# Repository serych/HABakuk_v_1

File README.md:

# HABakuk Pico Balloon Tracker Board

## Introduction:

Design of this board is based on excelent Alain's (K1FM) [K1FM-Pico-Balloon version 1.3](https://github.com/adecarolis).  Why I didn't use Alain's board directly and made my own PCB forked from his design? I was thinking about WSPR balloon tracker design for a long time (approximately 2-3 years) and I wanted simple board with ATmega328, Si5351 and Ublox GPS with possibility to switch peripheries off. From the board designs I found on the Internet, K1FM board met my original ideas the most but:  
- I wanted to power the board by solar panels via MPPT regulator (theorethicaly only two 50 x 25 mm panels would be enought to supply the board)
- I wanted the HF filter, but bypassable to test if the signal penetration is better with or without the filter 
- I'm designing my boards in KiCAD now, so I wanted to redraw the design completely (it is better than trying to import Eagle files) 

## Board construction:
The board includes MPPT power converter based on the SPV1040 chip and the values of the discrete components around it are calculated using [STMicroelectronics eDesignSuite](https://eds.st.com/photovoltaic/) using input parameters Voc = 1200 mV, Imp = 500 mA (measured on two solar panels in series) and Vmp = 930 mV, Imp = 450 mA (my estimation). There is connector for THT electrolytic capacitor serving as the energy store on the board. 

HF filter can be bypassed using **JP1** by scratching off solder jumper contact 1 (which is bridged on PCB by default) and soldering contact 3. 

I'm not sure if the measurement of solar panel voltage by the ATmega will not interfere with the SPV1040 power converter function, so I placed **JP2** on the board (bridged by default) which can be easily scratched off to break the (solar panel -> AD converter input) connection in the case of any problems.
                                                                                                          
The board is designed as 4 layers (only 3 layers used) thin PCB (it has thicknes of 0.8 mm only to reduce the weight of the PCB). Also there is filled zone (GND) only on one side of the board to reduce the weight. All the components except the Ublox GPS module are placed on the top side of the board to make the reflow soldering possible in the amateur conditions.  GPS module on the back side of the board should be soldered as the last component by the soldering iron.      

## Software: 
The recommended softwares are [OrionWSPR](https://github.com/ve3wmb/OrionWspr) or [GeminiWSPR](https://github.com/adecarolis/GeminiWspr)

## Production and real tests
The board will be ordered in [LJCPCB](https://jlcpcb.com/) and I will add here the link to reorder it.

**The board was not yet produced nor tested!** 

Jakub Šerých, serych@panska.cz, [https://jakub.serych.cz](https://jakub.serych.cz) (web only in Czech language)

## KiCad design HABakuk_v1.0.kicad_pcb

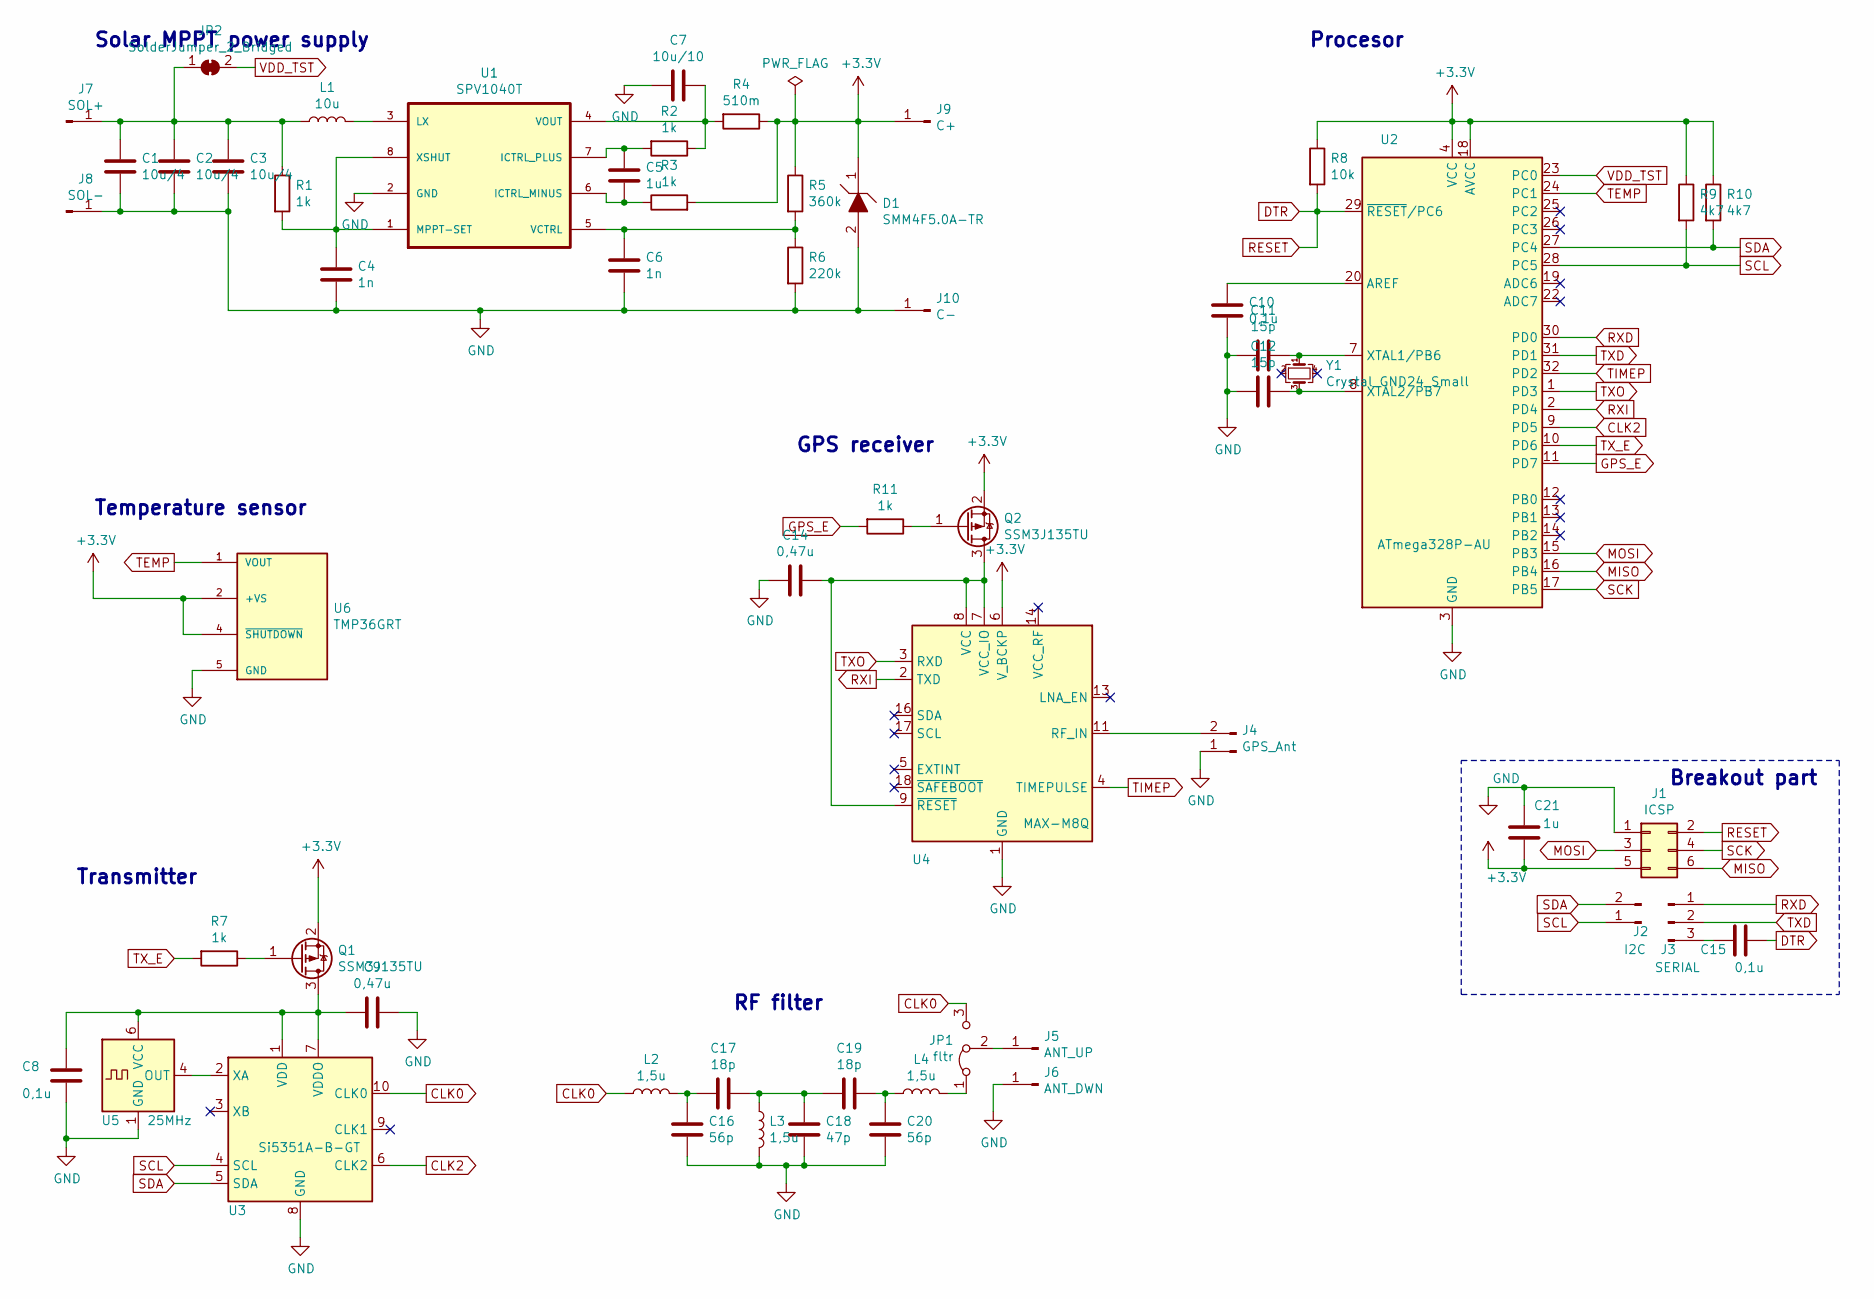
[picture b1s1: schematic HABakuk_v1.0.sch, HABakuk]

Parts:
C1, C2, C3: 10u/4; C_0603_1608Metric
C4, C6: 1n; C_0603_1608Metric
C5, C21: 1u; C_0603_1608Metric
C7: 10u/10; C_0805_2012Metric
C8, C10, C15: 0,1u; C_0603_1608Metric
C9, C14: 0,47u; C_0603_1608Metric
C11, C12: 15p; C_0603_1608Metric
C16, C20: 56p; C_0603_1608Metric
C17, C19: 18p; C_0603_1608Metric
C18: 47p; C_0603_1608Metric
D1: SMM4F5.0A-TR; STMITE; Mouser Part Number 511-SMM4F5.0A-TR
J1: ICSP; PinHeader_2x03_P2.54mm_Vertical
J2: I2C; PinHeader_1x02_P2.54mm_Vertical
J3: SERIAL; PinHeader_1x03_P2.54mm_Vertical
J4: GPS_Ant; PinHeader_1x02_P2.54mm_Vertical
J5: ANT_UP; PinHeader_1x01_P2.54mm_Vertical
J6: ANT_DWN; PinHeader_1x01_P2.54mm_Vertical
J7: SOL+; PinHeader_1x01_P2.54mm_Vertical
J8: SOL-; PinHeader_1x01_P2.54mm_Vertical
J9: C+; PinHeader_1x01_P2.54mm_Vertical
J10: C-; PinHeader_1x01_P2.54mm_Vertical
JP1: fltr; SolderJumper-3_P1.3mm_Bridged12_Pad1.0x1.5mm_NumberLabels
JP2: SolderJumper_2_Bridged; SolderJumper-2_P1.3mm_Bridged_Pad1.0x1.5mm
L1: 10u; L_Taiyo-Yuden_MD-3030
L2, L3, L4: 1,5u; L_0603_1608Metric
Q1, Q2: SSM3J135TU; SOT-23
R1, R2, R3, R7, R11: 1k; R_0603_1608Metric
R4: 510m; R_0603_1608Metric
R5: 360k; R_0603_1608Metric
R6: 220k; R_0603_1608Metric
R8: 10k; R_0603_1608Metric
R9, R10: 4k7; R_0603_1608Metric
U1: SPV1040T; TSSOP-8_4.4x3mm_P0.65mm
U2: ATmega328P-AU; TQFP-32_7x7mm_P0.8mm
U3: Si5351A-B-GT; MSOP-10_3x3mm_P0.5mm
U4: MAX-M8Q; ublox_MAX
U5: 25MHz; Oscillator_SMD_Kyocera_2520-6Pin_2.5x2.0mm
U6: TMP36GRT; SOT-23-5; PARTREV H
Y1: Crystal_GND24_Small; Crystal_SMD_5032-4Pin_5.0x3.2mm

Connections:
+3V3: C21.2, D1.1, J1.5, J9.1, Q1.2 (S), Q2.2 (S), R3.2, R4.1, R5.1, R8.1, R9.1, R10.1, U2.4 (VCC), U2.6 (VCC), U2.18 (AVCC), U4.6 (V_BCKP), U6.2 (+VS), U6.4 (~SHUTDOWN)
CLK0: JP1.3 (B), L2.1, U3.10 (CLK0)
CLK2: U2.9 (PD5), U3.6 (CLK2)
DTR: C15.1, J1.2, R8.2, U2.29 (~RESET~/PC6)
GND: C1.2, C2.2, C3.2, C4.2, C6.2, C7.2, C8.2, C9.1, C10.2, C11.2, C12.2, C14.2, C16.2, C18.2, C20.2, C21.1, D1.2, J1.1, J4.1, J6.1, J8.1, J10.1, L3.2, R6.2, U1.2 (GND), U2.3 (GND), U2.5 (GND), U2.21 (GND), U3.8 (GND), U4.1 (GND), U4.10 (GND), U4.12 (GND), U5.1 (GND), U5.3 (GND), U6.5 (GND)
GPS_E: R11.2, U2.11 (PD7)
MISO: J1.6, U2.16 (PB4)
MOSI: J1.3, U2.15 (PB3)
unnamed: C1.1, C2.1, C3.1, J7.1, JP2.1 (A), L1.1, R1.1
unnamed: C4.1, R1.2, U1.1 (MPPT-SET), U1.8 (XSHUT)
unnamed: C5.1, R2.2, U1.7 (ICTRL_PLUS)
unnamed: C5.2, R3.1, U1.6 (ICTRL_MINUS)
unnamed: C6.1, R5.2, R6.1, U1.5 (VCTRL)
unnamed: C7.1, R2.1, R4.2, U1.4 (VOUT)
unnamed: C8.1, C9.2, Q1.3 (D), U3.1 (VDD), U3.7 (VDDO), U5.6 (VCC)
unnamed: C10.1, U2.20 (AREF)
unnamed: C11.1, U2.7 (XTAL1/PB6), Y1.1
unnamed: C12.1, U2.8 (XTAL2/PB7), Y1.3
unnamed: C14.1, Q2.3 (D), U4.7 (VCC_IO), U4.8 (VCC), U4.9 (~RESET)
unnamed: C15.2, J3.3
unnamed: C16.1, C17.2, L2.2
unnamed: C17.1, C18.1, C19.2, L3.1
unnamed: C19.1, C20.1, L4.1
unnamed: J4.2, U4.11 (RF_IN)
unnamed: J5.1, JP1.2 (C)
unnamed: JP1.1 (A), L4.2
unnamed: L1.2, U1.3 (LX)
unnamed: Q1.1 (G), R7.1
unnamed: Q2.1 (G), R11.1
unnamed: U3.2 (XA), U5.4 (OUT)
RXD: J3.1, U2.30 (PD0)
RXI: U2.2 (PD4), U4.2 (TXD)
SCK: J1.4, U2.17 (PB5)
SCL: J2.1, R9.2, U2.28 (PC5), U3.4 (SCL)
SDA: J2.2, R10.2, U2.27 (PC4), U3.5 (SDA)
TEMP: U2.24 (PC1), U6.1 (VOUT)
TIMEP: U2.32 (PD2), U4.4 (TIMEPULSE)
TXD: J3.2, U2.31 (PD1)
TXO: U2.1 (PD3), U4.3 (RXD)
TX_E: R7.2, U2.10 (PD6)
VDD_TST: JP2.2 (B), U2.23 (PC0)

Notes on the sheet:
Breakout part
Transmitter
RF filter
Temperature sensor
GPS receiver
Solar MPPT power supply
Procesor

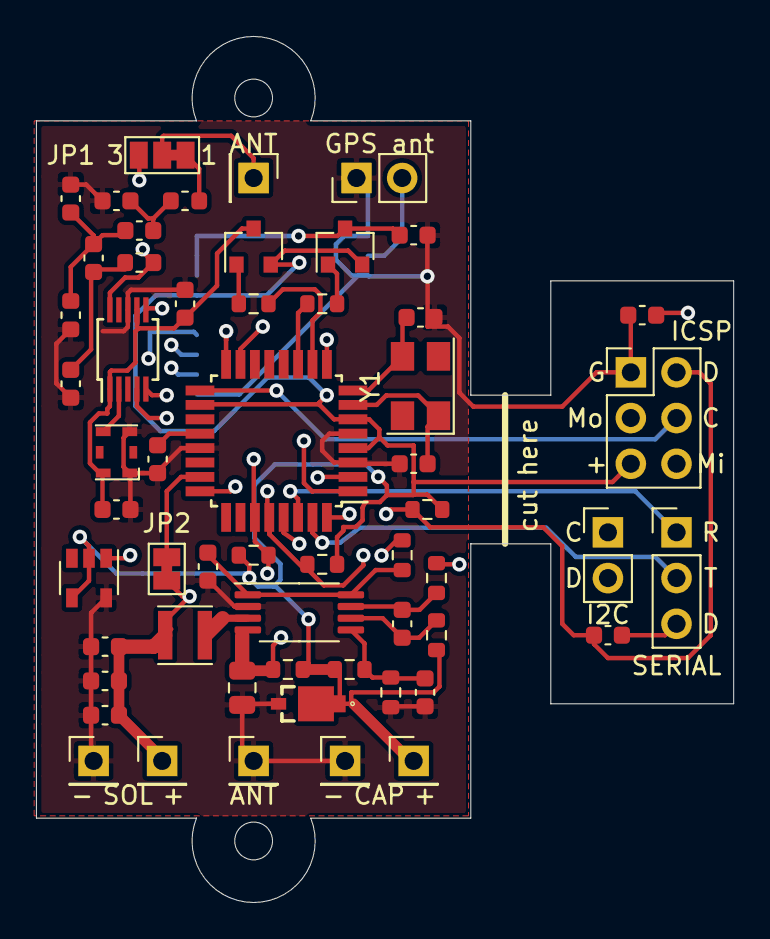
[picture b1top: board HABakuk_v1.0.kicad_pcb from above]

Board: 4 copper layers, 38.7 x 48.1 mm, 57 parts (1 on the bottom side), 41 nets.

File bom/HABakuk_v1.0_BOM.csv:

"Id";"Designator";"Package";"Quantity";"Designation";"Supplier and ref";
1;"D1";"STMITE";1;"SMM4F5.0A-TR";;;
2;"J10";"PinHeader_1x01_P2.54mm_Vertical";1;"C-";;;
3;"J9";"PinHeader_1x01_P2.54mm_Vertical";1;"C+";;;
4;"J8";"PinHeader_1x01_P2.54mm_Vertical";1;"SOL-";;;
5;"J7";"PinHeader_1x01_P2.54mm_Vertical";1;"SOL+";;;
6;"J6";"PinHeader_1x01_P2.54mm_Vertical";1;"ANT_DWN";;;
7;"J5";"PinHeader_1x01_P2.54mm_Vertical";1;"ANT_UP";;;
8;"J4";"PinHeader_1x02_P2.54mm_Vertical";1;"GPS_Ant";;;
9;"J3";"PinHeader_1x03_P2.54mm_Vertical";1;"SERIAL";;;
10;"J2";"PinHeader_1x02_P2.54mm_Vertical";1;"I2C";;;
11;"JP2";"SolderJumper-2_P1.3mm_Bridged_Pad1.0x1.5mm";1;"SolderJumper_2_Bridged";;;
12;"REF**,REF**";"MountingHole_2.1mm";2;"MountingHole_2.1mm";;;
13;"Y1";"Crystal_SMD_Abracon_ABM8G-4Pin_3.2x2.5mm";1;"Crystal_GND24_Small";;;
14;"U6";"SOT-23-5";1;"TMP36GRT";;;
15;"U5";"Oscillator_SMD_Kyocera_2520-6Pin_2.5x2.0mm";1;"25MHz";;;
16;"U4";"ublox_MAX";1;"MAX-M8Q";;;
17;"U3";"MSOP-10_3x3mm_P0.5mm";1;"Si5351A-B-GT";;;
18;"U2";"TQFP-32_7x7mm_P0.8mm";1;"ATmega328P-AU";;;
19;"U1";"TSSOP-8_4.4x3mm_P0.65mm";1;"SPV1040T";;;
20;"R11,R7,R3,R2,R1";"R_0603_1608Metric";5;"1k";;;
21;"R10,R9";"R_0603_1608Metric";2;"4k7";;;
22;"R8";"R_0603_1608Metric";1;"10k";;;
23;"R6";"R_0603_1608Metric";1;"220k";;;
24;"R5";"R_0603_1608Metric";1;"360k";;;
25;"R4";"R_0603_1608Metric";1;"510m";;;
26;"Q2,Q1";"SOT-23";2;"SSM3J135TU";;;
27;"L4,L3,L2";"L_0603_1608Metric";3;"1,5u";;;
28;"L1";"L_Taiyo-Yuden_MD-3030";1;"10u";;;
29;"JP1";"SolderJumper-3_P1.3mm_Bridged12_Pad1.0x1.5mm_NumberLabels";1;"fltr";;;
30;"J1";"PinHeader_2x03_P2.54mm_Vertical";1;"ICSP";;;
31;"C21,C5";"C_0603_1608Metric";2;"1u";;;
32;"C20,C16";"C_0603_1608Metric";2;"56p";;;
33;"C19,C17";"C_0603_1608Metric";2;"18p";;;
34;"C18";"C_0603_1608Metric";1;"47p";;;
35;"C15,C10,C8";"C_0603_1608Metric";3;"0,1u";;;
36;"C14,C9";"C_0603_1608Metric";2;"0,47u";;;
37;"C12,C11";"C_0603_1608Metric";2;"15p";;;
38;"C7";"C_0805_2012Metric";1;"10u/10";;;
39;"C6,C4";"C_0603_1608Metric";2;"1n";;;
40;"C3,C2,C1";"C_0603_1608Metric";3;"10u/4";;;

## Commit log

2021-05-31 Little corrections of README and tmp directory deletion
2021-06-02 Added BOMs, modified 8 MHz crystal footprint
2021-06-02 Added BOMs
2021-06-03 Fabrication files added
